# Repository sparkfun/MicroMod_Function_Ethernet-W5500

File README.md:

SparkFun MicroMod Ethernet Function Board - W5500
========================================

[*SparkFun MicroMod Ethernet Function Board - W5500 (COM-18708)*](https://www.sparkfun.com/products/18708)

The SparkFun MicroMod Ethernet Function Board - W5500 provides Ethernet network connection as well as Power-over-Ethernet capabilities to a MicroMod project.

The W5500 Ethernet Controller from WIZnet is a TCP/IP embedded Ethernet controller that uses SPI communication protocol to allow up to eight independent sockets operate simultaneously. The W5500 SPI interface operates at up to 80MHz and supports fast SPI for high speed Ethernet communication. The chip also includes a Wake on Lan (WOL) operation and power down mode to help conserve power.

The board uses a Ag9900m Power-over-Ethernet (PoE) DC/DC converter module to power MicroMod assemblies from a PoE source such as a router or network switch. The DC/DC converter supplies 9 Watts @5V to connected devices. This Function Board configures the PoE supply voltage to the IEEE802.3af Alternate B power scheme. This power scheme uses the spare pairs in the Ethernet cable (4,5 and 7,8) for positive and negative DC voltage, isolating power delivery from the data lines.

Repository Contents
-------------------

* **/Documents** - Datasheet, Appnotes.
* **/Firmware** - HTTP Test.
* **/Hardware** - Eagle design files (.brd, .sch)

Documentation
-------------

* **[Hookup Guide](https://learn.sparkfun.com/tutorials/micromod-ethernet-function-board---w5500-hookup-guide)** - A basic Hookup Guide to get started with the MicroMod Ethernet Function Board - W5500.

Product Versions
----------------
* [COM-18708](https://www.sparkfun.com/products/18708) - Initial release

Version History
---------------
* v1.0 - Initial Release 

License Information
-------------------

This product is _**open source**_! 

Please review the LICENSE.md file for license information. 

If you have any questions or concerns on licensing, please contact technical support on our [SparkFun forums](https://forum.sparkfun.com/viewforum.php?f=152).

Distributed as-is; no warranty is given.

- Your friends at SparkFun.

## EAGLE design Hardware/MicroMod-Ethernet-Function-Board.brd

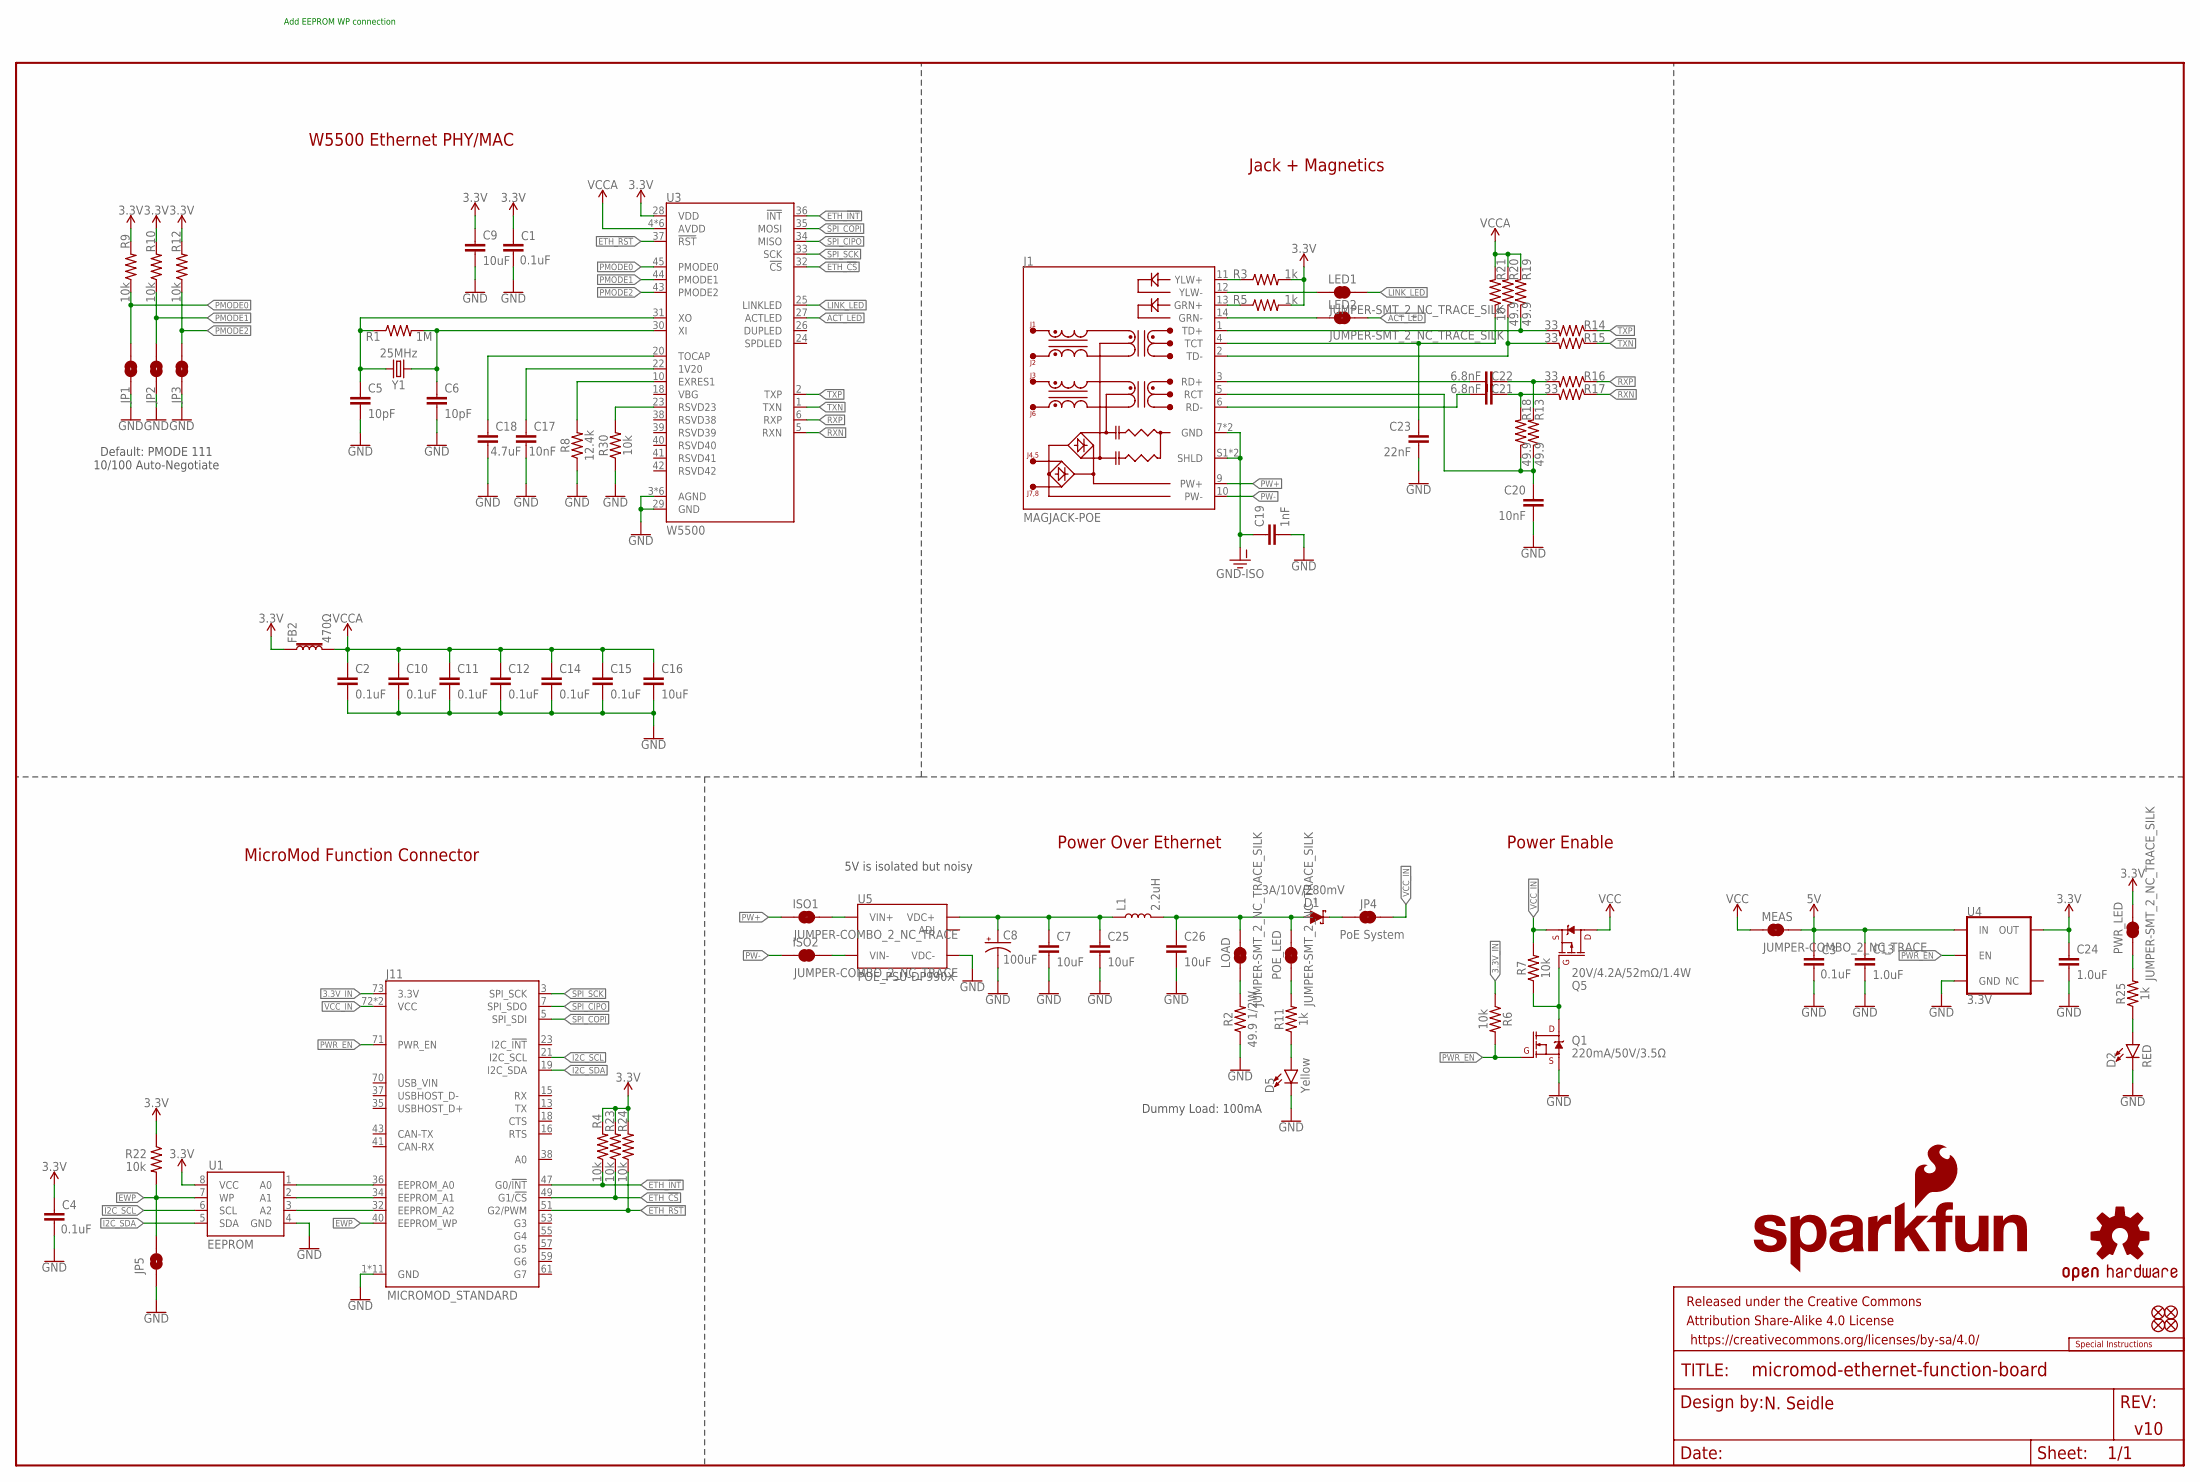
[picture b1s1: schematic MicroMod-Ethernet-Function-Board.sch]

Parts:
C1, C2, C3, C4, C10, C11, C12, C14, C15: 0.1uF; 0603
C5, C6: 10pF; 0603
C7, C25, C26: 10uF; 0805
C8: 100uF; PANASONIC_D
C9, C16: 10uF; 0603
C13, C24: 1.0uF; 0603
C17, C20: 10nF; 0603
C18: 4.7uF; 0603
C19: 1nF; 1206
C21, C22: 6.8nF; 0603
C23: 22nF; 0603
D1: 3A/10V/280mV; SOD-323
D2: RED; LED-0603
D5: Yellow; LED-0603
FB2: 470Ω; 0603
FD1, FD2, FD3, FD4: FIDUCIALUFIDUCIAL; FIDUCIAL-MICRO
FRAME1: FRAME-LEDGER; CREATIVE_COMMONS
ISO1, ISO2: JUMPER-COMBO_2_NC_TRACE; COMBO-JUMPER_2_NC_TRACE
J1: MAGJACK-POE; MAGJACK-SYM_LED
J11: MICROMOD_STANDARD; M.2-CARD-E-22_FUNCTION_STANDARD
JP1, JP2, JP3, JP5: JUMPER-SMT_2_NO_SILK; SMT-JUMPER_2_NO_SILK
JP4: PoE System; SMT-JUMPER_2_NC_TRACE_SILK
L1: 2.2uH; 0805-WIDE
LED1, LED2: JUMPER-SMT_2_NC_TRACE_SILK; SMT-JUMPER_2_NC_TRACE_SILK
LOAD: JUMPER-SMT_2_NC_TRACE_SILK; SMT-JUMPER_2_NC_TRACE_SILK
LOGO1: SFE_LOGO_NAME_FLAME.1_INCH; SFE_LOGO_NAME_FLAME_.1
LOGO2: SPECIAL_INSTRUCTIONS-ORDERING; ORDERING_INSTRUCTIONS
LOGO3: OSHW-LOGOMINI; OSHW-LOGO-MINI
MEAS: JUMPER-COMBO_2_NC_TRACE; COMBO-JUMPER_2_NC_TRACE
POE_LED: JUMPER-SMT_2_NC_TRACE_SILK; SMT-JUMPER_2_NC_TRACE_SILK
PWR_LED: JUMPER-SMT_2_NC_TRACE_SILK; SMT-JUMPER_2_NC_TRACE_SILK
Q1: 220mA/50V/3.5Ω; SOT23-3
Q5: 20V/4.2A/52mΩ/1.4W; SOT23-3
R1: 1M; 0603
R2: 49.9 1/2W; 1206
R3, R5, R11, R25: 1k; 0603
R4, R6, R7, R9, R10, R12, R22, R23, R24, R30: 10k; 0603
R8: 12.4k; 0603
R13, R18, R19, R20: 49.9; 0603
R14, R15, R16, R17: 33; 0603
R21: 10; 0603
U1: EEPROM; SO08
U3: W5500; LQFP-48
U4: 3.3V; SOT23-5
U5: POE_PSU-DP990X; DP990X
Y1: 25MHz; CRYSTAL-SMD-2.0X1.6MM

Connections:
3.3V: C1.1, C4.1, C9.1, C24.1, FB2.1, PWR_LED.2, R3.2, R4.2, R5.2, R9.2, R10.2, R12.2, R22.1, R23.2, R24.2, U1.8 (VCC), U3.28 (VDD), U4.5 (OUT); also elsewhere on the board
3.3V_IN: J11.73 (3.3V), R6.1
5V: C3.1, C13.1, MEAS.2, MEAS.4 (2), U4.1 (IN)
5V_FILTER: C26.1, D1.A, L1.2, LOAD.2, POE_LED.2
5V_RAW: C7.1, C8.+, C25.1, L1.1, U5.1 (VDC+), U5.2 (VDC+)
A0: J11.36 (EEPROM_A0), U1.1 (A0)
A1: J11.34 (EEPROM_A1), U1.2 (A1)
A2: J11.32 (EEPROM_A2), U1.3 (A2)
ACT_LED: LED2.2, U3.27 (ACTLED)
ETH_!CS!: J11.49 (G1/!CS!), R23.1, U3.32 (!CS!)
ETH_!INT!: J11.47 (G0/!INT!), R4.1, U3.36 (!INT!)
ETH_!RST!: J11.51 (G2/PWM), R24.1, U3.37 (!RST!)
EWP: J11.40 (EEPROM_WP), JP5.2, R22.2, U1.7 (WP)
GND: C1.2, C2.2, C3.2, C4.2, C5.2, C6.2, C7.2, C8.-, C9.2, C10.2, C11.2, C12.2, C13.2, C14.2, C15.2, C16.2, C17.2, C18.2, C19.2, C20.2, C23.2, C24.2, C25.2, C26.2, D2.C, D5.C, J11.1 (GND), J11.33 (GND), J11.39 (GND), J11.45 (GND), J11.75 (GND), J11.GND1 (GND), J11.GND2 (GND), J11.GND3 (GND), J11.GND4 (GND), J11.GND5 (GND), J11.GND6 (GND), JP1.1, JP2.1, JP3.1, JP5.1, Q1.2 (S), R2.1, R8.1, R30.1, U1.4 (GND), U3.3 (AGND), U3.9 (AGND), U3.14 (AGND), U3.16 (AGND), U3.19 (AGND), U3.29 (GND), U3.48 (AGND), U4.2 (GND), U5.3 (VDC-)
GND-ISO: C19.1, J1.7 (GND), J1.8 (GND), J1.S1 (SHLD), J1.S2 (SHLD); also elsewhere on the board
I2C_SCL: J11.21 (I2C_SCL), U1.6 (SCL)
I2C_SDA: J11.19 (I2C_SDA), U1.5 (SDA)
LINK_LED: LED1.2, U3.25 (LINKLED)
unnamed: C5.1, R1.1, U3.31 (XO), Y1.1
unnamed: C6.1, R1.2, U3.30 (XI), Y1.3 (2)
unnamed: J1.14 (GRN-), LED2.1
unnamed: J1.12 (YLW-), LED1.1
unnamed: D5.A, R11.1
unnamed: POE_LED.1, R11.2
unnamed 24: D1.C, JP4.1; also elsewhere on the board
unnamed: J1.13 (GRN+), R5.1
unnamed: LOAD.1, R2.2
unnamed: J1.11 (YLW+), R3.1
unnamed: Q1.3 (D), Q5.1 (G), R7.1
unnamed: R8.2, U3.10 (EXRES1)
unnamed: C17.1, U3.22 (1V20)
unnamed: C18.1, U3.20 (TOCAP)
unnamed: R30.2, U3.23 (RSVD23)
unnamed: PWR_LED.1, R25.2
unnamed: D2.A, R25.1
PMODE0: JP1.2, R9.1, U3.45 (PMODE0)
PMODE1: JP2.2, R10.1, U3.44 (PMODE1)
PMODE2: JP3.2, R12.1, U3.43 (PMODE2)
PW1+: ISO1.2, ISO1.4 (2), U5.5 (VIN+), U5.6 (VIN+)
PW1-: ISO2.2, ISO2.4 (2), U5.7 (VIN-), U5.8 (VIN-)
PW+: ISO1.1, ISO1.3 (1), J1.9 (PW+)
PW-: ISO2.1, ISO2.3 (1), J1.10 (PW-)
PWR_EN: J11.71 (PWR_EN), Q1.1 (G), R6.2, U4.3 (EN)
RCT: C20.1, J1.5 (RCT), R13.1, R18.1
RD+: C22.2, J1.3 (RD+); also elsewhere on the board
RD-: C21.2, J1.6 (RD-); also elsewhere on the board
RXN: R17.1, U3.5 (RXN)
RXN1: C21.1, R17.2, R18.2
RXP: R16.1, U3.6 (RXP)
RXP1: C22.1, R13.2, R16.2
SPI_CIPO: J11.7 (SPI_SDO), U3.34 (MISO)
SPI_COPI: J11.5 (SPI_SDI), U3.35 (MOSI)
SPI_SCK: J11.3 (SPI_SCK), U3.33 (SCK)
TCT: C23.1, J1.4 (TCT), R21.1
TD+: J1.1 (TD+), R14.2, R19.1; also elsewhere on the board
TD-: J1.2 (TD-), R15.2, R20.1; also elsewhere on the board
TXN: R15.1, U3.1 (TXN)
TXP: R14.1, U3.2 (TXP)
VCC: MEAS.1, MEAS.3 (1), Q5.3 (D)
VCCA: C2.1, C10.1, C11.1, C12.1, C14.1, C15.1, C16.1, FB2.2, R19.2, R20.2, R21.2, U3.4 (AVDD), U3.8 (AVDD), U3.11 (AVDD), U3.15 (AVDD), U3.17 (AVDD), U3.21 (AVDD)
VCC_IN: J11.72 (VCC), J11.74 (VCC), JP4.2, Q5.2 (S), R7.2; also elsewhere on the board

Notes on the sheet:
Power Over Ethernet
MicroMod Function Connector
5V is isolated but noisy
N. Seidle
v10
W5500 Ethernet PHY/MAC
Power Enable
Default: PMODE 111 10/100 Auto-Negotiate
Jack + Magnetics
Dummy Load: 100mA
Add EEPROM WP connection

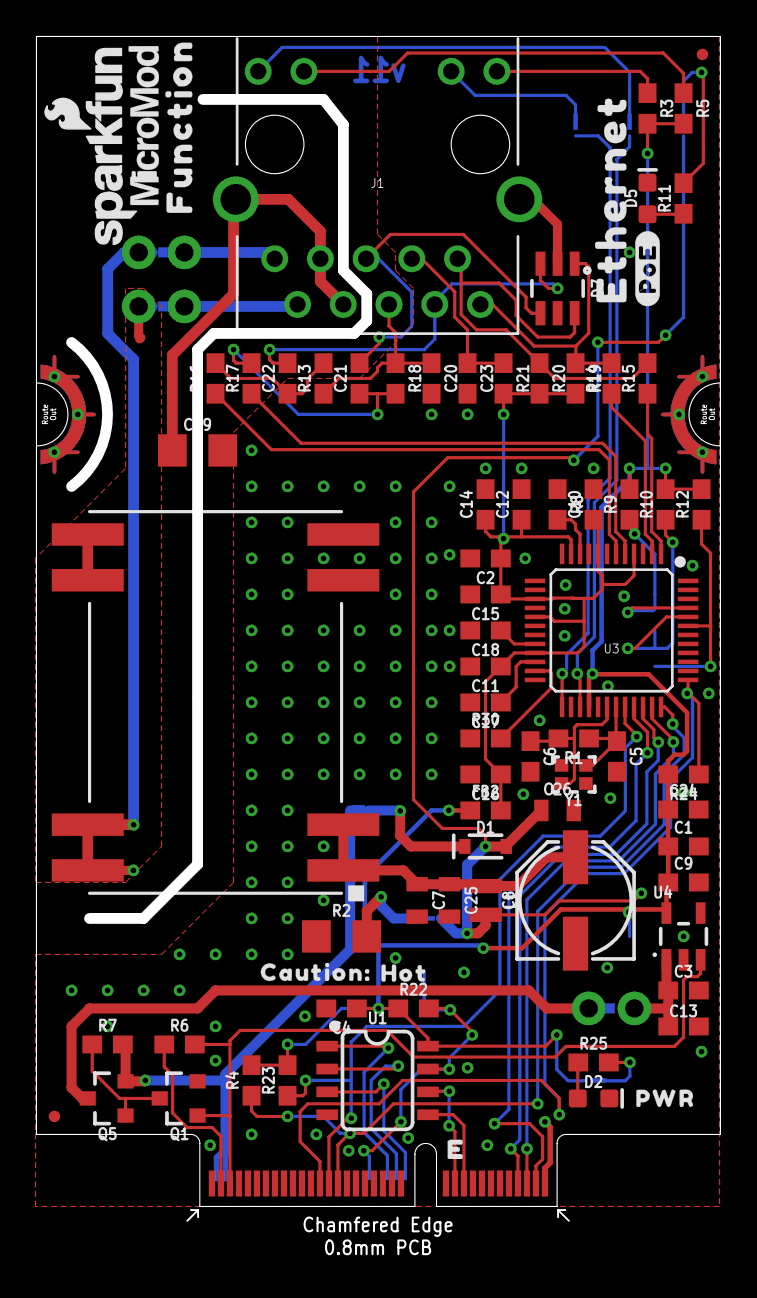
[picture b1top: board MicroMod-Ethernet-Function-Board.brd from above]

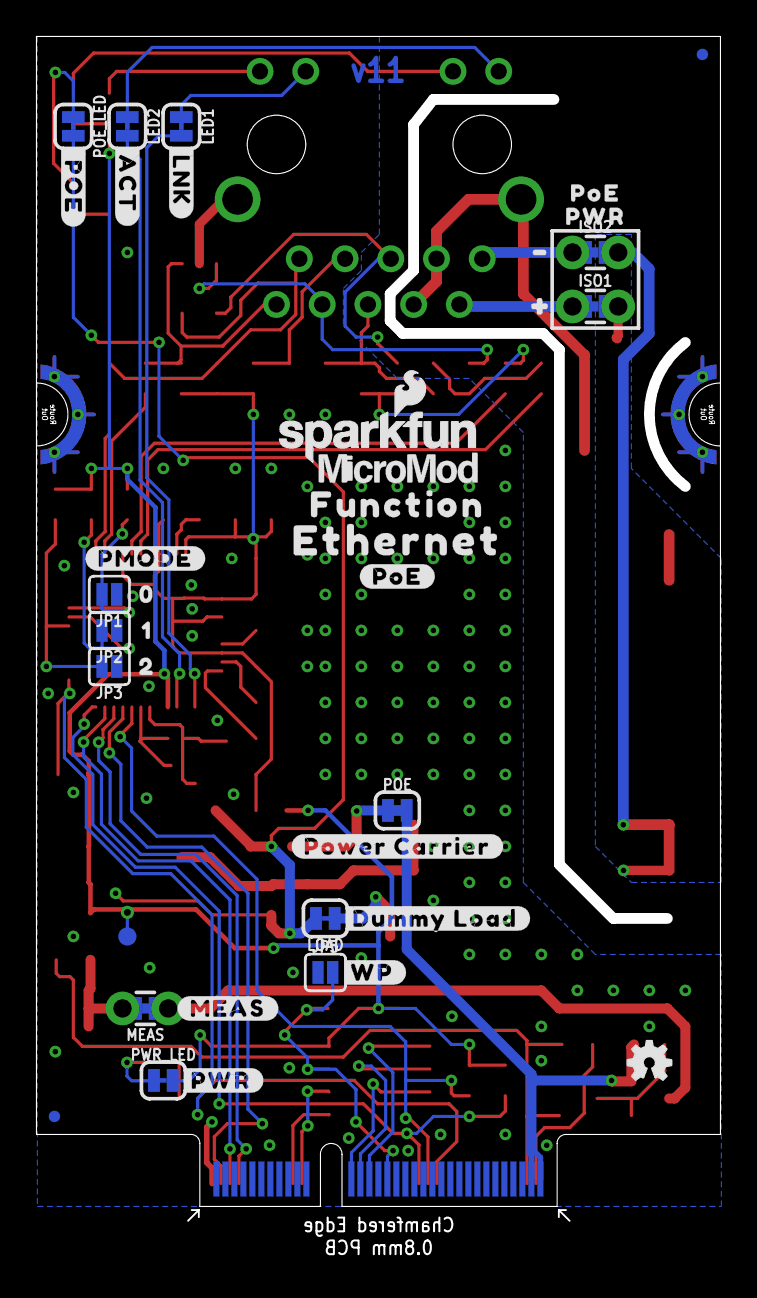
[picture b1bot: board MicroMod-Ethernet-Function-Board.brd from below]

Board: 2 copper layers, 38.0 x 65.8 mm, 117 parts (38 on the bottom side), 61 nets.

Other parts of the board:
D7: DT1042-04SO; SOT-23-6
LOGO4: SFE_LOGO_NAME_FLAME.1_INCH; SFE_LOGO_NAME_FLAME_.1
POE: SMT-JUMPER_2_NC_TRACE_SILK
TP1: TEST-POINT3X4; PAD.03X.04
U$1, U$17: ETHERNET0
U$2, U$18: #POE#0
U$3: #POWER_CARRIER#0
U$5: #DUMMY_LOAD#0
U$6: #WP#0
U$7: PWR0
U$8: #ACT#0
U$9: POE0
U$12: #LNK#1
U$13: #PMODE#0
U$14: 01
U$15: 12
U$16: 23
U$19: #0
U$20: CAUTION#0
U$21: HOT#1
U$22: #PWR#0
U$23: #_POE#0
U$24: PWR1
U$25: #1
U$26, U$27: FUNCTION0
U$28: #MEAS#3
U$37, U$63: MICROMOD_LOGO_.35

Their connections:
3.3V: TP1.1; also elsewhere on the board
GND-ISO: D7.2; also elsewhere on the board
unnamed 24: POE.1; also elsewhere on the board
RD+: D7.3; also elsewhere on the board
RD-: D7.4; also elsewhere on the board
TD+: D7.1; also elsewhere on the board
TD-: D7.6; also elsewhere on the board
VCC_IN: POE.2; also elsewhere on the board

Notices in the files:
parts and their libraries:
SparkFun-Aesthetics: Licensing: Creative Commons ShareAlike 4.0 International - https://creativecommons.org/licenses/by-sa/4.0
SparkFun-Aesthetics: Released under the Creative Commons Attribution Share-Alike 4.0 License
SparkFun-Aesthetics: https://creativecommons.org/licenses/by-sa/4.0
